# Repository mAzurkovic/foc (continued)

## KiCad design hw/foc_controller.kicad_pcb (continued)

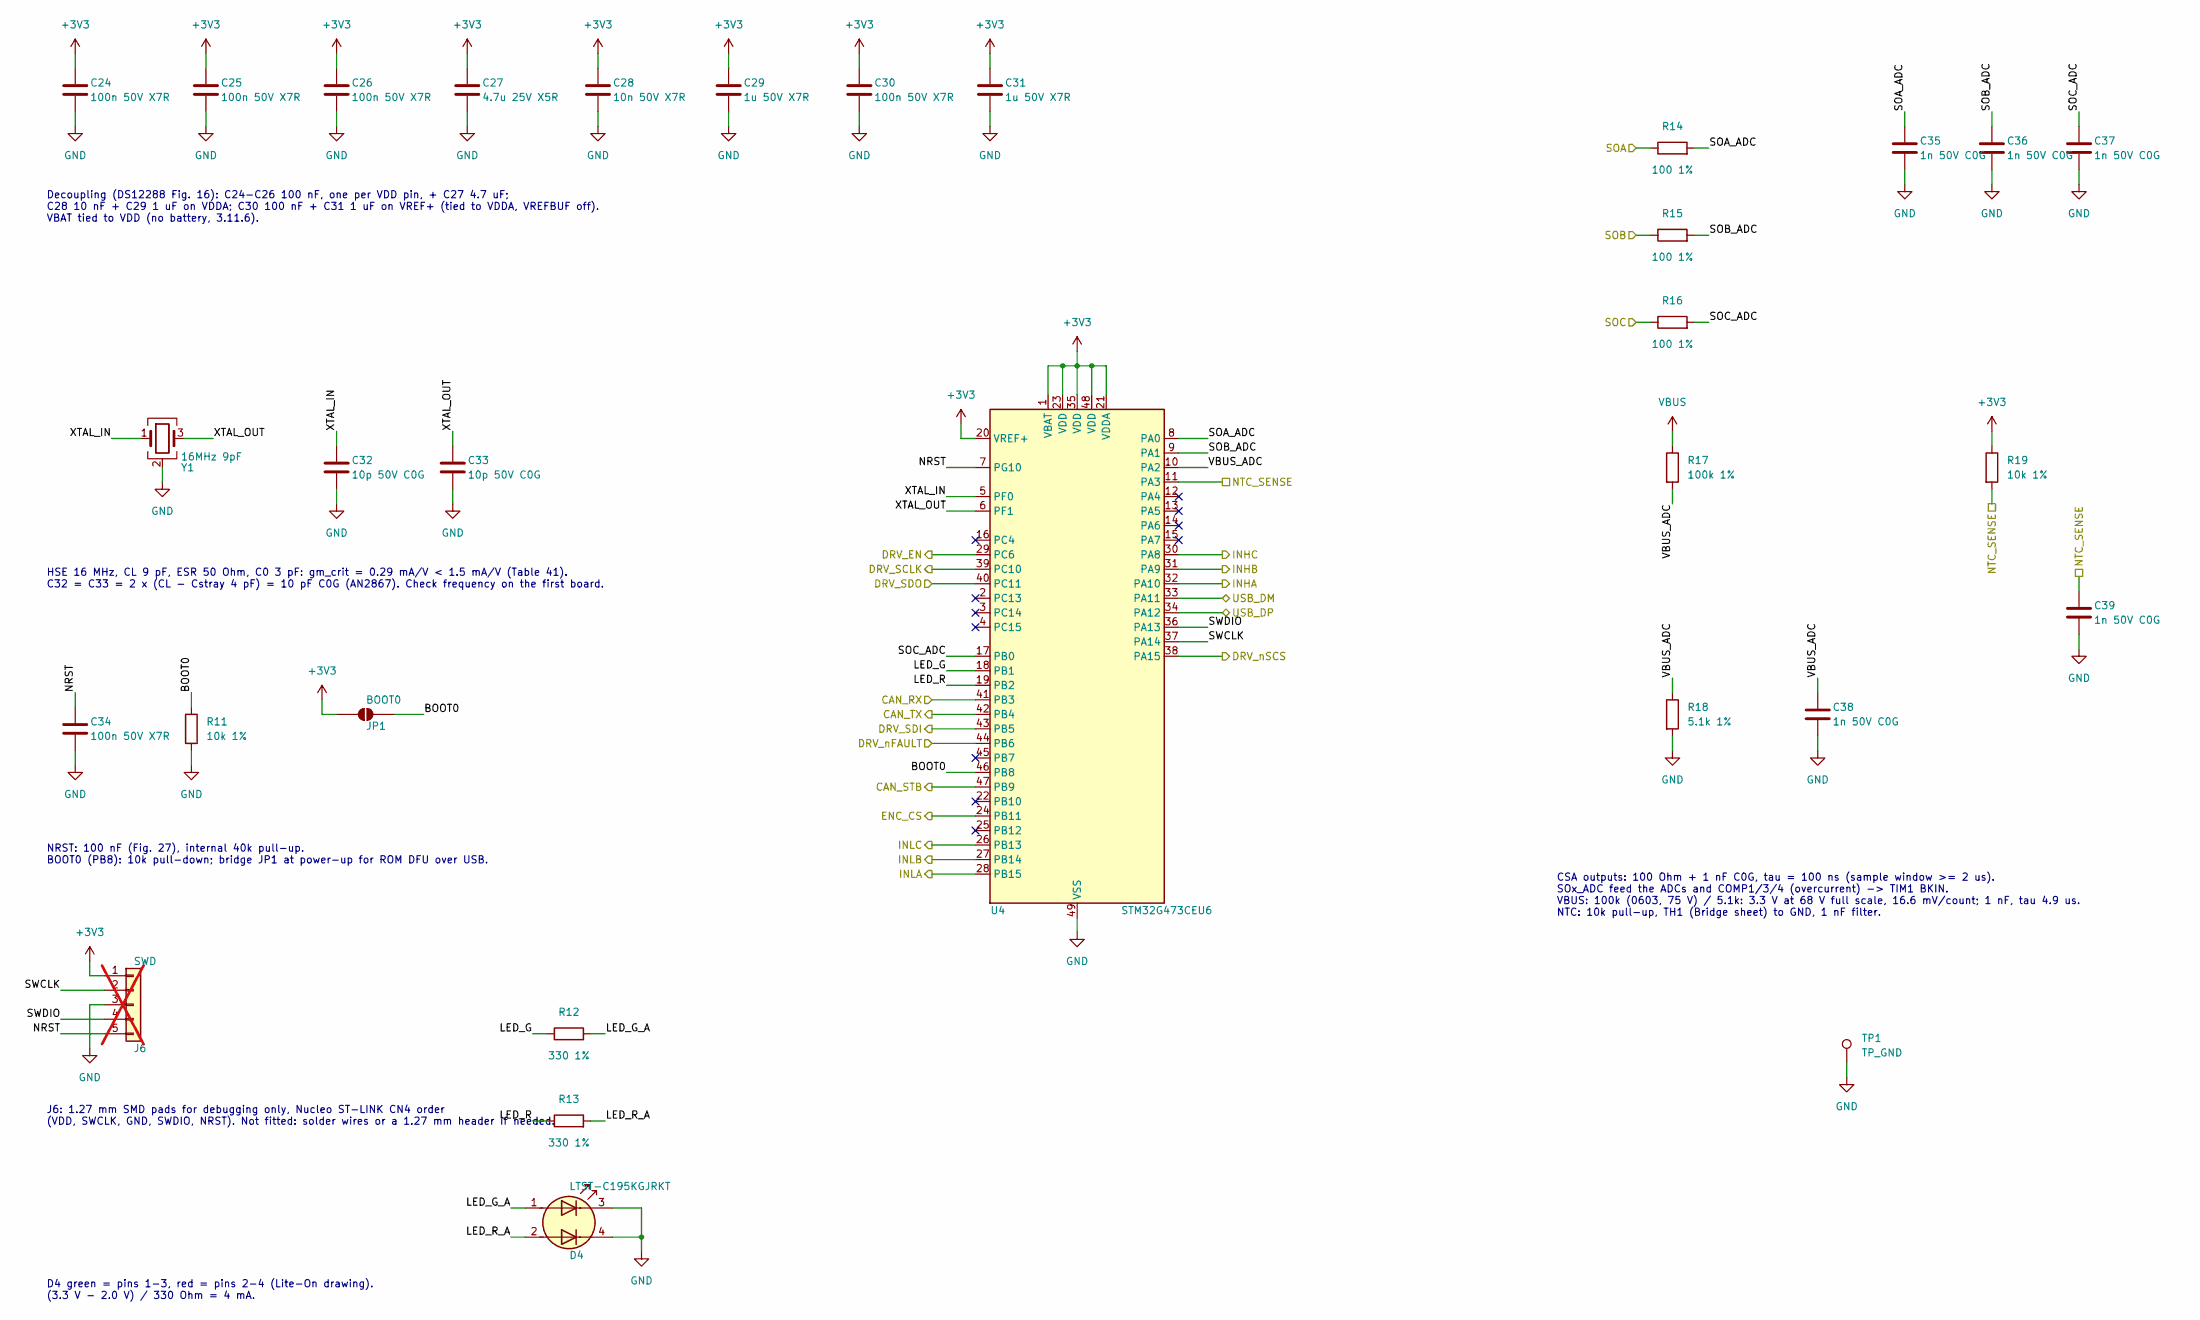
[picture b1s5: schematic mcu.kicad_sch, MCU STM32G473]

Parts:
C24, C25, C26, C30, C34: 100n 50V X7R; C_0402_1005Metric; MPN CL05B104KB54PNC; LCSC C307331
C27: 4.7u 25V X5R; C_0805_2012Metric; MPN CL21A475KAQNNNE; LCSC C1779
C28: 10n 50V X7R; C_0402_1005Metric; MPN CL05B103KB5NNNC; LCSC C15195
C29, C31: 1u 50V X7R; C_0805_2012Metric; MPN CL21B105KBFNNNE; LCSC C28323
C32, C33: 10p 50V C0G; C_0402_1005Metric; MPN CL05C100JB5NNNC; LCSC C32949
C35, C36, C37, C38, C39: 1n 50V C0G; C_0402_1005Metric; MPN CC0402JRNPO9BN102; LCSC C113780
D4: LTST-C195KGJRKT; LED-ARRAY-SMD_0603-4P-L1.6-W1.5-BR-RD; MPN LTST-C195KGJRKT; LCSC C125104
J6: SWD; SWD_Pads_1x05_P1.27mm_SMD; not fitted
JP1: BOOT0; SolderJumper-2_P1.3mm_Open_Pad1.0x1.5mm
R11, R19: 10k 1%; R_0402_1005Metric; MPN 0402WGF1002TCE; LCSC C25744
R12, R13: 330 1%; R_0402_1005Metric; MPN 0402WGF3300TCE; LCSC C25104
R14, R15, R16: 100 1%; R_0402_1005Metric; MPN 0402WGF1000TCE; LCSC C25076
R17: 100k 1%; R_0603_1608Metric; MPN 0603WAF1003T5E; LCSC C25803
R18: 5.1k 1%; R_0603_1608Metric; MPN 0603WAF5101T5E; LCSC C23186
TP1: TP_GND; TestPoint_Pad_D1.0mm
U4: STM32G473CEU6; QFN-48-1EP_7x7mm_P0.5mm_EP5.6x5.6mm; MPN STM32G473CEU6; LCSC C1342773
Y1: 16MHz 9pF; Crystal_SMD_3225-4Pin_3.2x2.5mm; MPN X322516MLB4SI; LCSC C13738

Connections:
+3V3: C24.1, C25.1, C26.1, C27.1, C28.1, C29.1, C30.1, C31.1, J6.1, JP1.1 (A), R19.1, U4.1 (VBAT), U4.20 (VREF+), U4.21 (VDDA), U4.23 (VDD), U4.35 (VDD), U4.48 (VDD); also elsewhere on the board
/CAN_RX: U4.41 (PB3); also elsewhere on the board
/CAN_STB: U4.47 (PB9); also elsewhere on the board
/CAN_TX: U4.42 (PB4); also elsewhere on the board
/DRV_EN: U4.29 (PC6); also elsewhere on the board
/DRV_SCLK: U4.39 (PC10); also elsewhere on the board
/DRV_SDI: U4.43 (PB5); also elsewhere on the board
/DRV_SDO: U4.40 (PC11); also elsewhere on the board
/DRV_nFAULT: U4.44 (PB6); also elsewhere on the board
/DRV_nSCS: U4.38 (PA15); also elsewhere on the board
/ENC_CS: U4.24 (PB11); also elsewhere on the board
/INHA: U4.32 (PA10); also elsewhere on the board
/INHB: U4.31 (PA9); also elsewhere on the board
/INHC: U4.30 (PA8); also elsewhere on the board
/INLA: U4.28 (PB15); also elsewhere on the board
/INLB: U4.27 (PB14); also elsewhere on the board
/INLC: U4.26 (PB13); also elsewhere on the board
/MCU/BOOT0: JP1.2 (B), R11.1, U4.46 (PB8)
/MCU/LED_G: R12.1, U4.18 (PB1)
/MCU/LED_G_A: D4.1 (A1), R12.2
/MCU/LED_R: R13.1, U4.19 (PB2)
/MCU/LED_R_A: D4.2 (A2), R13.2
/MCU/NRST: C34.1, J6.5, U4.7 (PG10)
/MCU/SOA_ADC: C35.1, R14.2, U4.8 (PA0)
/MCU/SOB_ADC: C36.1, R15.2, U4.9 (PA1)
/MCU/SOC_ADC: C37.1, R16.2, U4.17 (PB0)
/MCU/SWCLK: J6.2, U4.37 (PA14)
/MCU/SWDIO: J6.4, U4.36 (PA13)
/MCU/VBUS_ADC: C38.1, R17.2, R18.1, U4.10 (PA2)
/MCU/XTAL_IN: C32.1, U4.5 (PF0), Y1.1
/MCU/XTAL_OUT: C33.1, U4.6 (PF1), Y1.3
/NTC_SENSE: C39.1, R19.2, U4.11 (PA3); also elsewhere on the board
/SOA: R14.1; also elsewhere on the board
/SOB: R15.1; also elsewhere on the board
/SOC: R16.1; also elsewhere on the board
/USB_DM: U4.33 (PA11); also elsewhere on the board
/USB_DP: U4.34 (PA12); also elsewhere on the board
GND: C24.2, C25.2, C26.2, C27.2, C28.2, C29.2, C30.2, C31.2, C32.2, C33.2, C34.2, C35.2, C36.2, C37.2, C38.2, C39.2, D4.3 (K1), D4.4 (K2), J6.3, R11.2, R18.2, TP1.1 (1_1), U4.49 (VSS), Y1.2 (G), Y1.4 (G); also elsewhere on the board
VBUS: R17.1; also elsewhere on the board

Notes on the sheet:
Decoupling (DS12288 Fig. 16): C24-C26 100 nF, one per VDD pin, + C27 4.7 uF; C28 10 nF + C29 1 uF on VDDA; C30 100 nF + C31 1 uF on VREF+ (tied to VDDA, VREFBUF off). VBAT tied to VDD (no battery, 3.11.6).
HSE 16 MHz, CL 9 pF, ESR 50 Ohm, C0 3 pF: gm_crit = 0.29 mA/V < 1.5 mA/V (Table 41). C32 = C33 = 2 x (CL - Cstray 4 pF) = 10 pF C0G (AN2867). Check frequency on the first board.
CSA outputs: 100 Ohm + 1 nF C0G, tau = 100 ns (sample window >= 2 us). SOx_ADC feed the ADCs and COMP1/3/4 (overcurrent) -> TIM1 BKIN. VBUS: 100k (0603, 75 V) / 5.1k: 3.3 V at 68 V full scale, 16.6 mV/count; 1 nF, tau 4.9 us. NTC: 10k pull-up, TH1 (Bridge sheet) to GND, 1 nF filter.
D4 green = pins 1-3, red = pins 2-4 (Lite-On drawing). (3.3 V - 2.0 V) / 330 Ohm = 4 mA.
J6: 1.27 mm SMD pads for debugging only, Nucleo ST-LINK CN4 order (VDD, SWCLK, GND, SWDIO, NRST). Not fitted: solder wires or a 1.27 mm header if needed.
NRST: 100 nF (Fig. 27), internal 40k pull-up. BOOT0 (PB8): 10k pull-down; bridge JP1 at power-up for ROM DFU over USB.

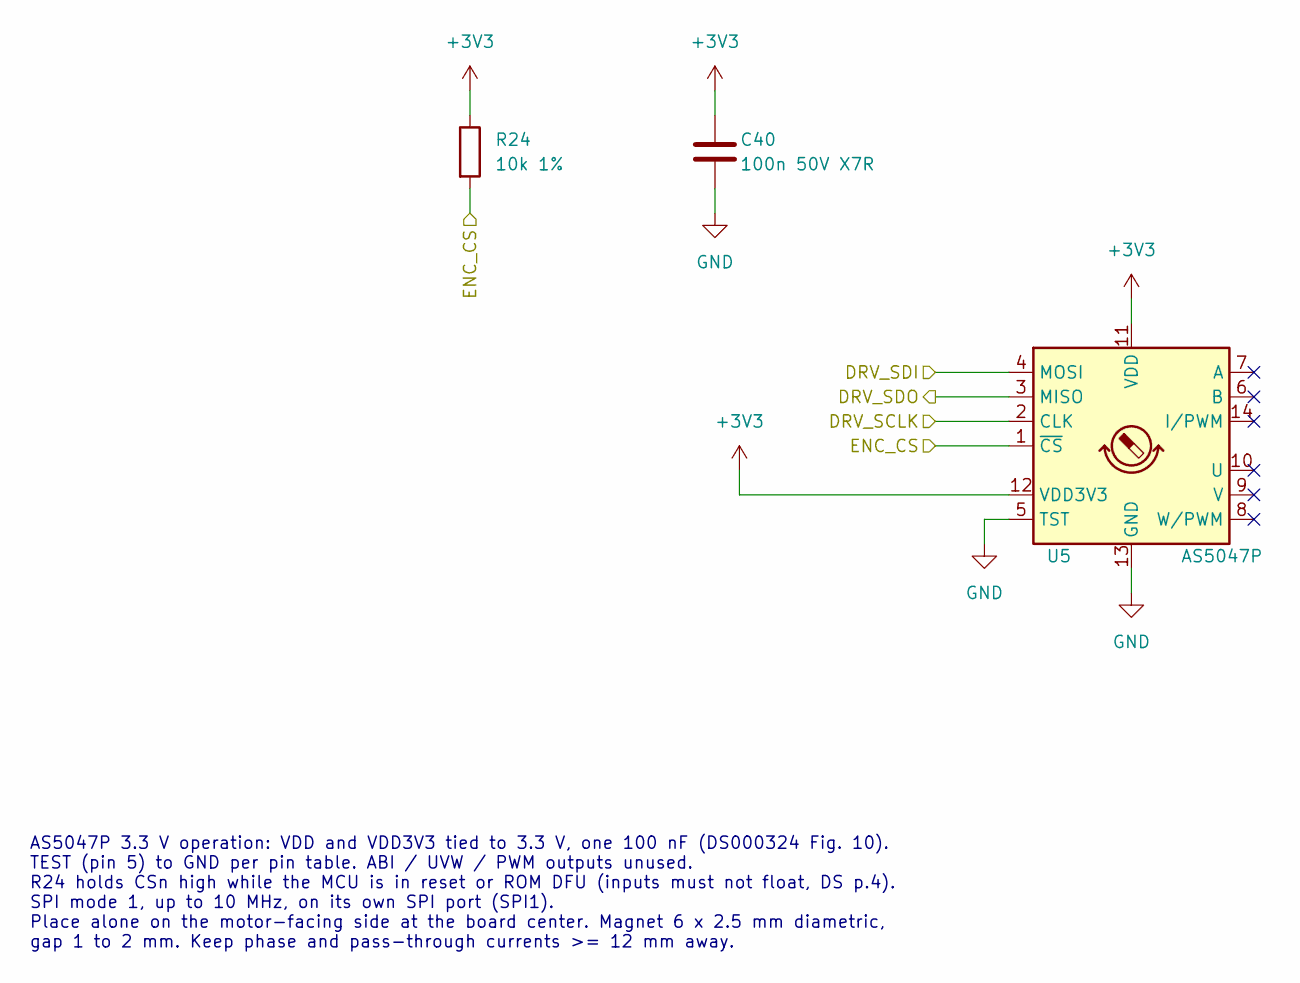
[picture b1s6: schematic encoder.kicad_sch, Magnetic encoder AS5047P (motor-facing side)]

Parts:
C40: 100n 50V X7R; C_0402_1005Metric; MPN CL05B104KB54PNC; LCSC C307331
R24: 10k 1%; R_0402_1005Metric; MPN 0402WGF1002TCE; LCSC C25744
U5: AS5047P; TSSOP-14_4.4x5mm_P0.65mm; MPN AS5047P-ATSM; LCSC C962063

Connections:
+3V3: C40.1, R24.1, U5.11 (VDD), U5.12 (VDD3V3); also elsewhere on the board
/DRV_SCLK: U5.2 (CLK); also elsewhere on the board
/DRV_SDI: U5.4 (MOSI); also elsewhere on the board
/DRV_SDO: U5.3 (MISO); also elsewhere on the board
/ENC_CS: R24.2, U5.1 (~CS); also elsewhere on the board
GND: C40.2, U5.5 (TST), U5.13 (GND); also elsewhere on the board

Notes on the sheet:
AS5047P 3.3 V operation: VDD and VDD3V3 tied to 3.3 V, one 100 nF (DS000324 Fig. 10). TEST (pin 5) to GND per pin table. ABI / UVW / PWM outputs unused. R24 holds CSn high while the MCU is in reset or ROM DFU (inputs must not float, DS p.4). SPI mode 1, up to 10 MHz, on its own SPI port (SPI1). Pla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

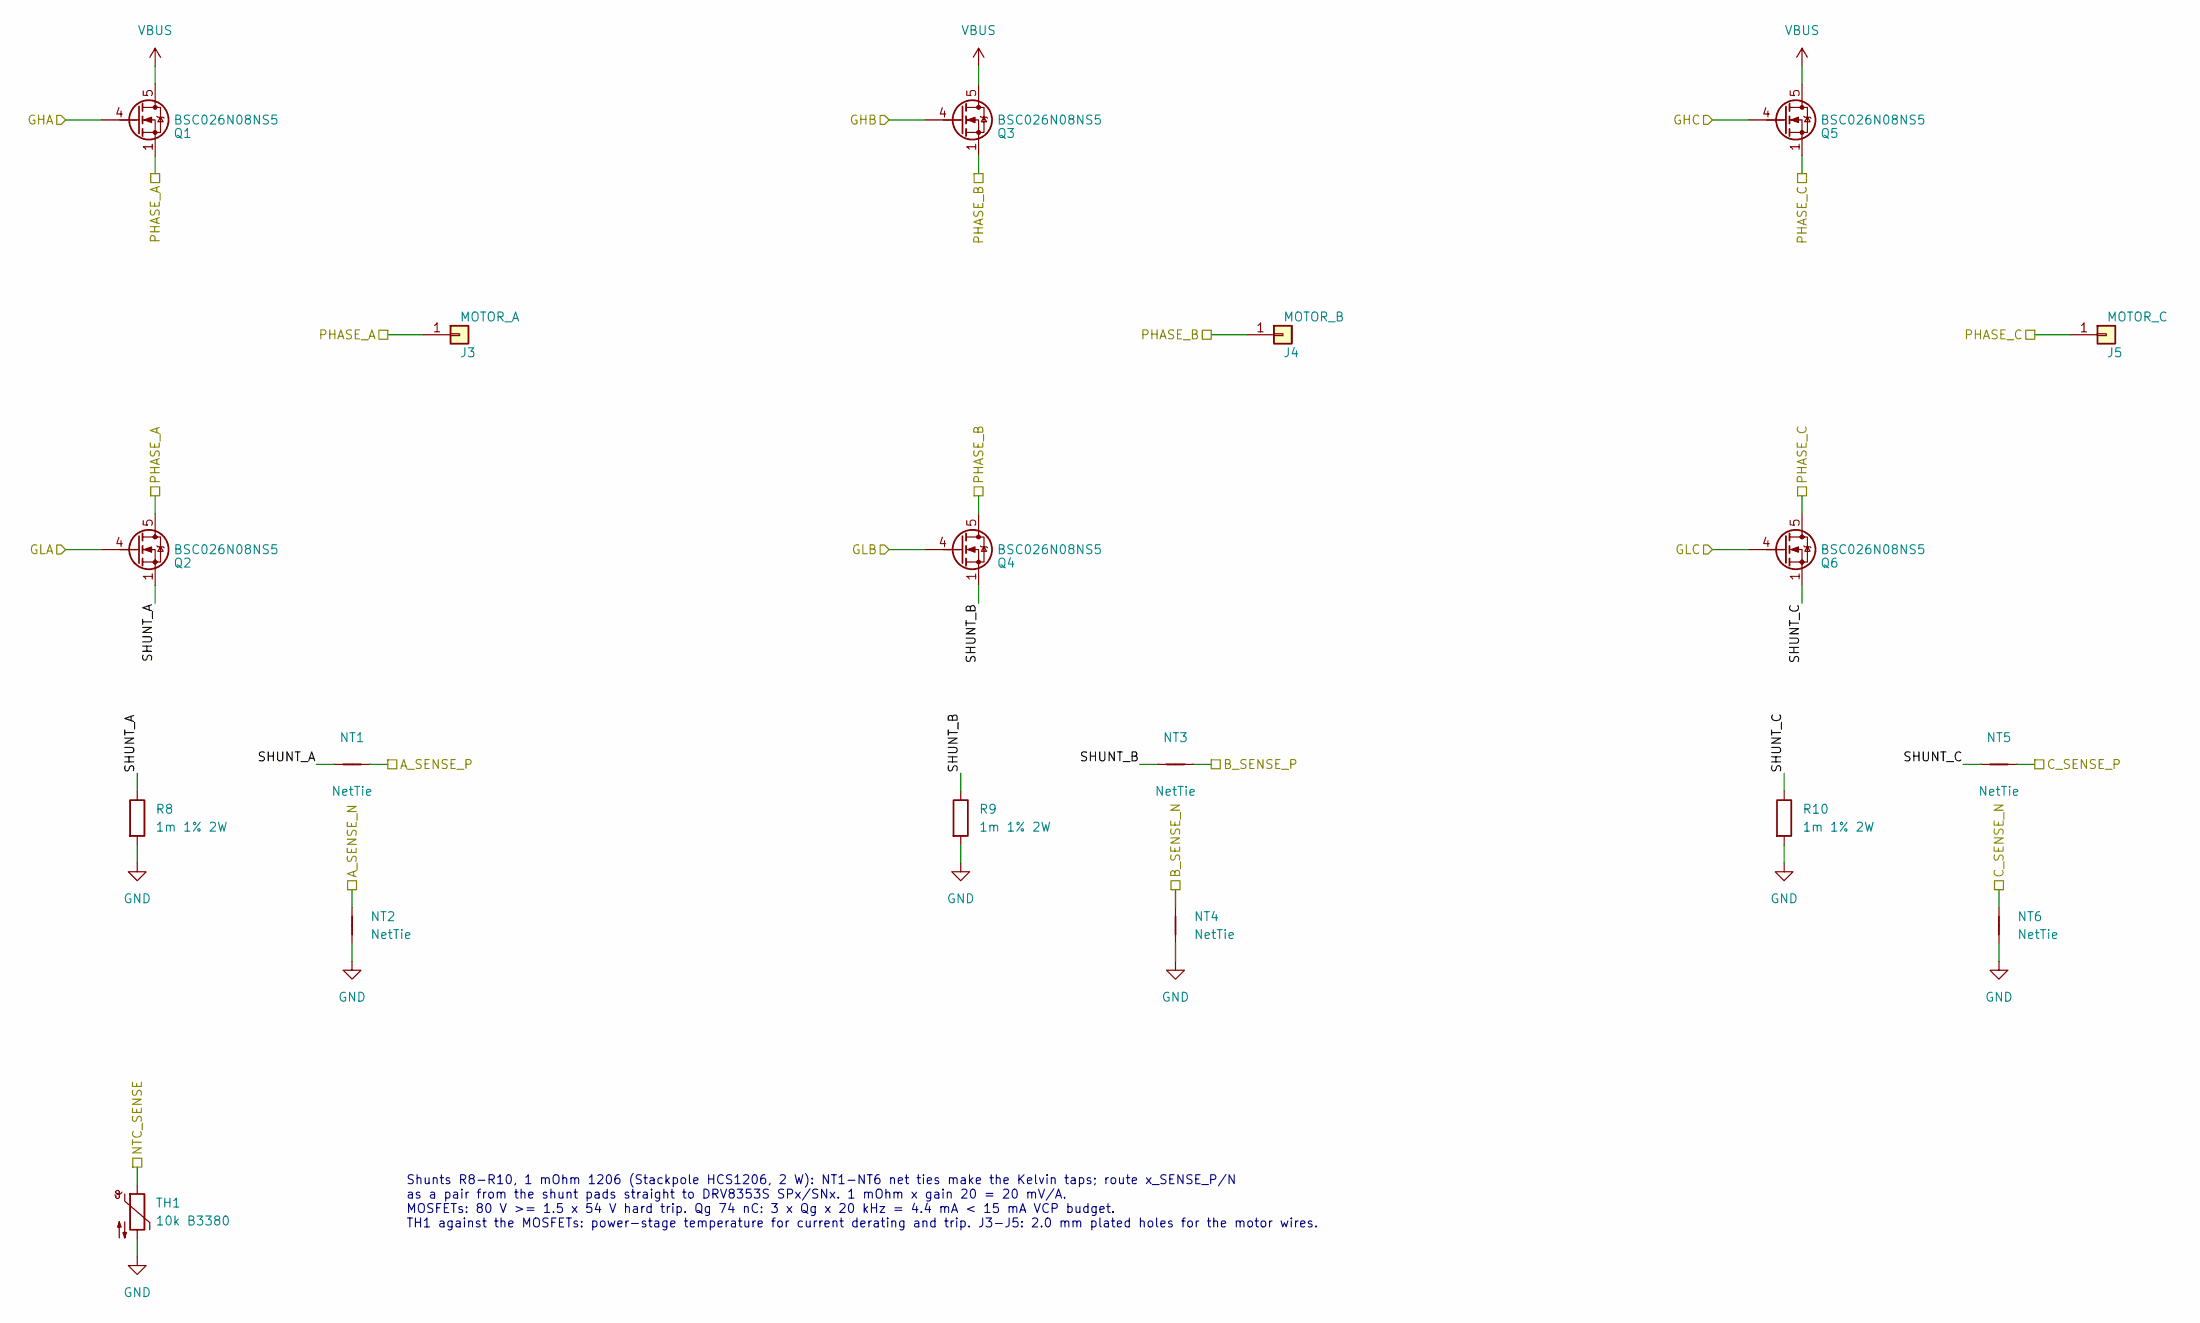
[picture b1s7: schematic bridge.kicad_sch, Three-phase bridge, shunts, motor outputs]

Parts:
J3: MOTOR_A; SolderWire-2sqmm_1x01_D2mm_OD3.9mm
J4: MOTOR_B; SolderWire-2sqmm_1x01_D2mm_OD3.9mm
J5: MOTOR_C; SolderWire-2sqmm_1x01_D2mm_OD3.9mm
NT1, NT2, NT3, NT4, NT5, NT6: NetTie; NetTie-2_SMD_Pad0.5mm
Q1, Q2, Q3, Q4, Q5, Q6: BSC026N08NS5; Infineon_PG-TDSON-8_6.15x5.15mm; MPN BSC026N08NS5ATMA1; LCSC C5955453
R8, R9, R10: 1m 1% 2W; R_1206_Shunt_HCS1206; MPN HCS1206FT1L00; LCSC C4087826
TH1: 10k B3380; R_0402_1005Metric; MPN NCP15XH103F03RC; LCSC C77131

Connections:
/A_SENSE_N: NT2.2; also elsewhere on the board
/A_SENSE_P: NT1.2; also elsewhere on the board
/B_SENSE_N: NT4.2; also elsewhere on the board
/B_SENSE_P: NT3.2; also elsewhere on the board
/Bridge/SHUNT_A: NT1.1, Q2.1 (S), Q2.2 (S), Q2.3 (S), R8.1
/Bridge/SHUNT_B: NT3.1, Q4.1 (S), Q4.2 (S), Q4.3 (S), R9.1
/Bridge/SHUNT_C: NT5.1, Q6.1 (S), Q6.2 (S), Q6.3 (S), R10.1
/C_SENSE_N: NT6.2; also elsewhere on the board
/C_SENSE_P: NT5.2; also elsewhere on the board
/GHA: Q1.4 (G); also elsewhere on the board
/GHB: Q3.4 (G); also elsewhere on the board
/GHC: Q5.4 (G); also elsewhere on the board
/GLA: Q2.4 (G); also elsewhere on the board
/GLB: Q4.4 (G); also elsewhere on the board
/GLC: Q6.4 (G); also elsewhere on the board
/NTC_SENSE: TH1.1; also elsewhere on the board
/PHASE_A: J3.1 (Pin_1_1), Q1.1 (S), Q1.2 (S), Q1.3 (S), Q2.5 (D); also elsewhere on the board
/PHASE_B: J4.1 (Pin_1_1), Q3.1 (S), Q3.2 (S), Q3.3 (S), Q4.5 (D); also elsewhere on the board
/PHASE_C: J5.1 (Pin_1_1), Q5.1 (S), Q5.2 (S), Q5.3 (S), Q6.5 (D); also elsewhere on the board
GND: NT2.1, NT4.1, NT6.1, R8.2, R9.2, R10.2, TH1.2; also elsewhere on the board
VBUS: Q1.5 (D), Q3.5 (D), Q5.5 (D); also elsewhere on the board

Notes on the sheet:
Shunts R8-R10, 1 mOhm 1206 (Stackpole HCS1206, 2 W): NT1-NT6 net ties make the Kelvin taps; route x_SENSE_P/N as a pair from the shunt pads straight to DRV8353S SPx/SNx. 1 mOhm x gain 20 = 20 mV/A. MOSFETs: 80 V >= 1.5 x 54 V hard trip. Qg 74 nC: 3 x Qg x 20 kHz = 4.4 mA < 15 mA VCP budget. TH1 aga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

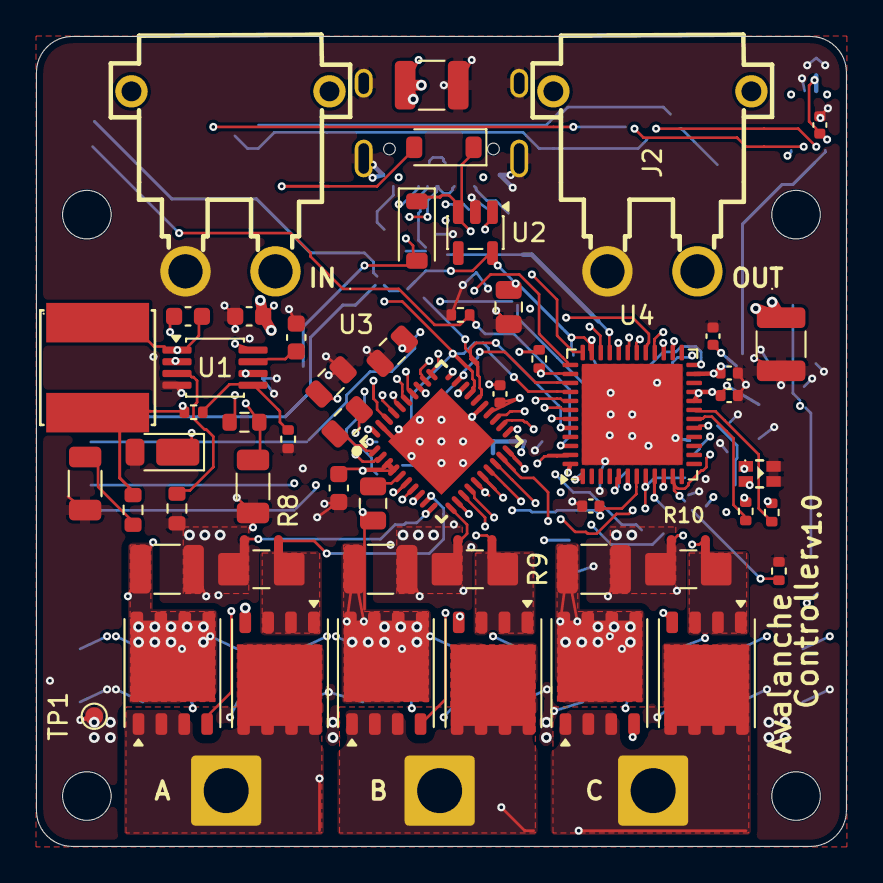
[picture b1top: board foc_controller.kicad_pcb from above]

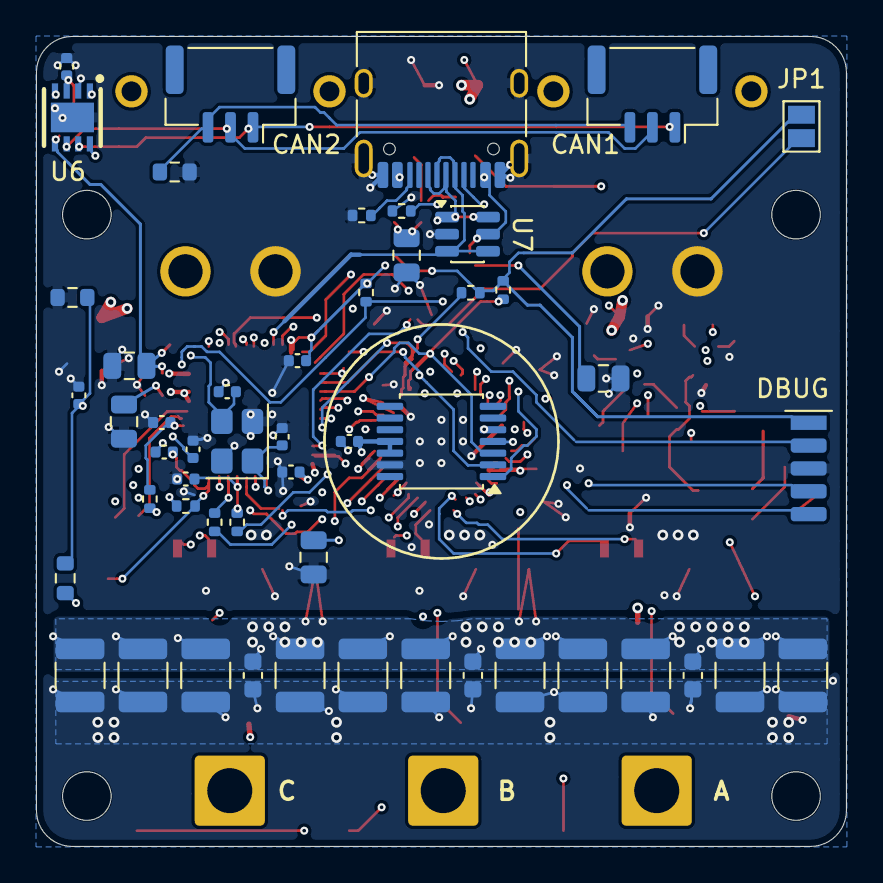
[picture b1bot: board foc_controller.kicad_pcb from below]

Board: 6 copper layers, 45.0 x 45.0 mm, 117 parts (51 on the bottom side), 77 nets.

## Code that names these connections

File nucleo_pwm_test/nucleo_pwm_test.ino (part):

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const uint8_t PIN_DRIVER_CS = D9;
const uint8_t PIN_EN_GATE = D6;
const uint8_t PIN_NFAULT = D5;
// PWM on PA8, PA9, PA10 (D7, D8, D2) = TIM1 CH1..3; current sense on PA0, PA1,
// PA4 (A0..A2) = ADC1 channels 0, 1, 4; bus voltage on PB0 (A3) = channel 8.
const uint32_t ADC_CHANNEL_A = 0;
const uint32_t ADC_CHANNEL_B = 1;
const uint32_t ADC_CHANNEL_C = 4;
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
